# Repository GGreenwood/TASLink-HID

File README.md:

# TASLink-HID
HID Joystick add-on for the Papilio Pro FPGA board. Developed for use with TASLink hardware.

## Schematics

## Layout

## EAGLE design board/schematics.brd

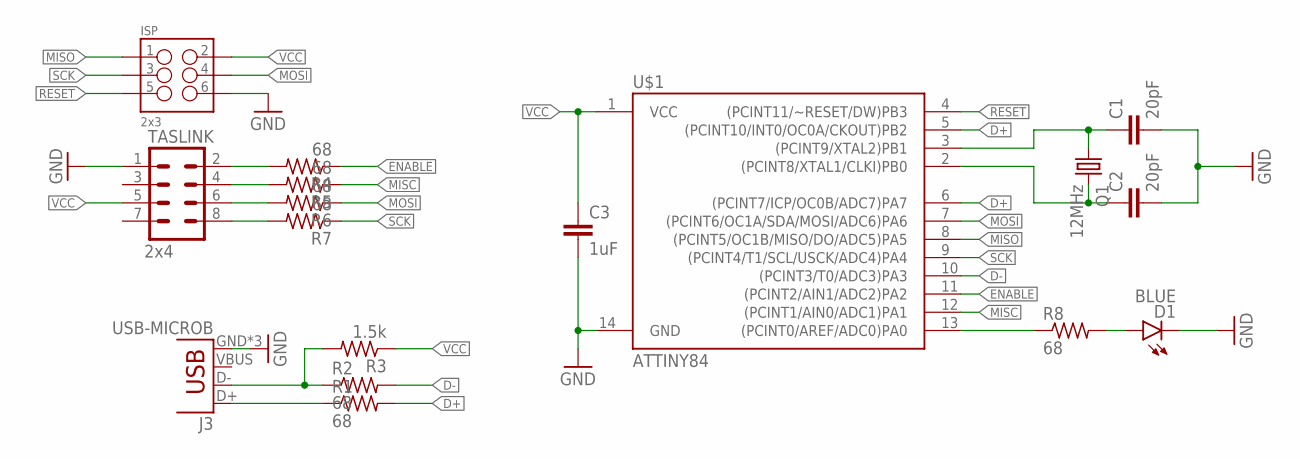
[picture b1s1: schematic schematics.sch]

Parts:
C1, C2: 20pF; C0603
C3: 1uF; C0603
D1: BLUE; LED-0603
ISP: 2x3; 2X3_POGO
J3: USB-MICROB
Q1: 12MHz; CTS406
R1, R2, R4, R5, R6, R7, R8: 68; R0603
R3: 1.5k; R0603
TASLINK: 2x4; 2X4
U$1: ATTINY84; SO14

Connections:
D+: R1.2, U$1.5 ((PCINT10/INT0/OC0A/CKOUT)PB2), U$1.6 ((PCINT7/ICP/OC0B/ADC7)PA7)
D-: R2.2, U$1.10 ((PCINT3/T0/ADC3)PA3)
ENABLE: R4.1, U$1.11 ((PCINT2/AIN1/ADC2)PA2)
GND: C1.2, C2.2, C3.2, D1.C, ISP.P$6 (6), J3.GND, J3.MT1 (GND), J3.MT2 (GND), TASLINK.1, U$1.14 (GND)
LED: R8.1, U$1.13 ((PCINT0/AREF/ADC0)PA0)
MISC: R5.1, U$1.12 ((PCINT1/AIN0/ADC1)PA1)
MISO: ISP.P$1 (1), U$1.8 ((PCINT5/OC1B/MISO/DO/ADC5)PA5)
MOSI: ISP.P$4 (4), R6.1, U$1.7 ((PCINT6/OC1A/SDA/MOSI/ADC6)PA6)
unnamed: C1.1, Q1.1, U$1.3 ((PCINT9/XTAL2)PB1)
unnamed: C2.1, Q1.3 (2), U$1.2 ((PCINT8/XTAL1/CLKI)PB0)
unnamed: J3.D+, R1.1
unnamed: J3.D-, R2.1, R3.2
unnamed: D1.A, R8.2
unnamed: R7.2, TASLINK.8
unnamed: R6.2, TASLINK.6
unnamed: R5.2, TASLINK.4
unnamed: R4.2, TASLINK.2
RESET: ISP.P$5 (5), U$1.4 ((PCINT11/~RESET/DW)PB3)
SCK: ISP.P$3 (3), R7.1, U$1.9 ((PCINT4/T1/SCL/USCK/ADC4)PA4)
VCC: C3.1, ISP.P$2 (2), R3.1, TASLINK.5, U$1.1 (VCC)

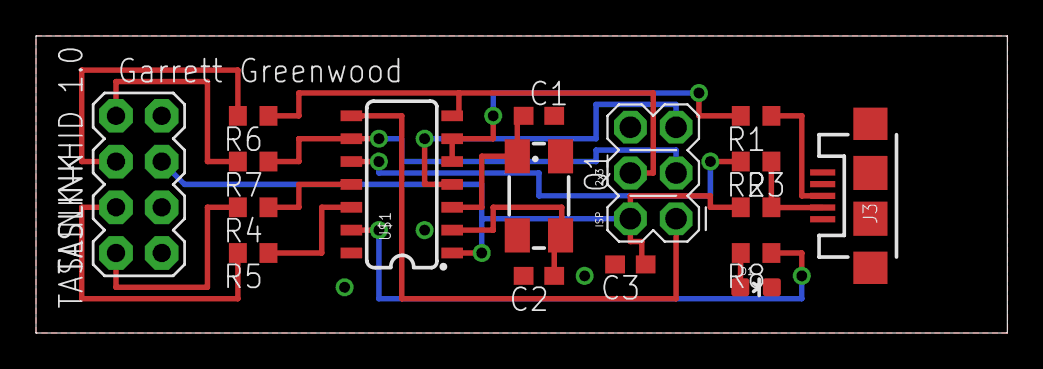
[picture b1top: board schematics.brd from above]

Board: 2 copper layers, 54.0 x 16.5 mm, 17 parts (0 on the bottom side), 20 nets.

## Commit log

2016-03-17 Initial release

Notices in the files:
parts and their libraries:
SparkFun-LED: Licensing: Creative Commons ShareAlike 4.0 International - https://creativecommons.org/licenses/by-sa/4.0
